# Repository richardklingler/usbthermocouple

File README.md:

# 2-channel USB thermocouple sensor

### Introduction

This is my first ever published project on Github, so most probably not error free (o;

It is a small 60mm x 80mm USB device which reads out temperatures from two K-type thermocouple sensors via MAX31855 converters.
As the main controller a STM32F070CBT6 was chosen due to the simplicity in setting up the STM32CubeIDE and configure it for USB CDC mode.

[**STM32CubeIDE**](https://www.st.com/en/development-tools/stm32cubeide.html)

For schematic and PCB design the great KiCAD software was used:

[**KiCAD**](https://www.kicad.org/)

### Repository layout

| Folder | Content |
|---|---|
| `kicad/usb_thermo_logger` | Schematic, PCB layout, 3D preview, datasheets |
| `openscad` | Front and back panels for the enclosure (`.scad` and `.stl`) |
| `stm32/USB_Thermologger_2` | Firmware, STM32CubeIDE project |
| `python` | PyQt5 logger application for the **previous** firmware (see below) |

### How it works

The device is powered from the USB port and registers as a USB CDC serial interface, so no driver is needed:

| OS | Device |
|---|---|
| Linux | `/dev/ttyACM0` |
| macOS | `/dev/cu.usbmodem…` |
| Windows | `COMx` |

The baud rate setting doesn't matter.

| USB descriptor | Value |
|---|---|
| Vendor ID / Product ID | `0x1209` / `0x5304` ([pid.codes](https://pid.codes/1209/5304/)) |
| Manufacturer | Klingler Engineering |
| Product | USB Thermocouple Logger |
| Serial number | Unique per device, derived from the STM32 chip ID |

The device doesn't send anything on its own. The host software asks for a measurement whenever it wants one, and adds its own timestamps.
This keeps the firmware simple: no clock to set, no drift, and the polling interval is completely up to the host.

The MAX31855 converts about 10 times per second, so polling faster than every 100 ms just returns the same value again.

### USB commands

| Command | Reply | Function |
|---|---|---|
| `?` | `24.50,23.75` | Read all channels |
| `*IDN?` | `Klingler Engineering,TC2,208438763130,1.0.0` | Identify the device |
| `C?` | `2` | Number of channels |
| `X1704` | none | Enter the DFU bootloader (see [Firmware update](#firmware-update)) |

Every reply is one line terminated by CR LF (`\r\n`).

Commands don't need a line ending, but **each command has to arrive in one piece**. The firmware looks at every USB packet on its own, so send the whole command with a single write.
A terminal program like `screen` sends every keystroke separately, which only works for the single-character `?`.

Send one command and wait for its reply before sending the next one.

### Identification

`*IDN?` follows the usual convention of measurement instruments and returns four comma-separated fields:

| Field | Example | Meaning |
|---|---|---|
| 1 | `Klingler Engineering` | Manufacturer |
| 2 | `TC2` | Model |
| 3 | `208438763130` | Serial number, identical to the USB serial number |
| 4 | `1.0.0` | Firmware version |

`C?` returns the number of thermocouple channels. Host software should use it instead of assuming a fixed number, so it also works with devices that have more channels.

### Reply format

After a `?`, the device replies with one line containing one value per channel, separated by commas. On the 2-channel device:

| Reply | Meaning |
|---|---|
| `24.50,23.75` | Both channels have a thermocouple |
| `24.50,-` | Only channel 1 has a valid reading |
| `-,23.75` | Only channel 2 has a valid reading |
| `-,-` | No valid reading on either channel |

Values are in degrees Celsius with a resolution of 0.25 °C. Negative temperatures are reported as negative values, e.g. `-12.25`.
The MAX31855 reports -270 °C to +1800 °C; the usable range of a K-type thermocouple itself is roughly -200 °C to +1350 °C.

### Errors

A `-` is sent for a channel when the MAX31855 reports a fault:

- thermocouple not connected (open circuit)
- thermocouple shorted to GND
- thermocouple shorted to VCC

### Quick test

With `screen` on Linux or macOS, type `?` and the reply appears (exit with Ctrl-A, then K):

```
screen /dev/ttyACM0 115200
```

For the other commands, use Python and [pyserial](https://pypi.org/project/pyserial/), which sends each command in one write:

```python
import serial

with serial.Serial('/dev/ttyACM0', timeout=1) as port:   # macOS: /dev/cu.usbmodem..., Windows: COM3
    for command in (b'*IDN?', b'C?', b'?'):
        port.write(command)
        print(command.decode(), '->', port.readline().decode().strip())
```

A simple logger that polls once per second and adds host timestamps:

```python
import serial, time
from datetime import datetime

with serial.Serial('/dev/ttyACM0', timeout=1) as port:
    while True:
        port.reset_input_buffer()
        port.write(b'?')
        reply = port.readline().decode(errors='replace').strip()
        print(f"{datetime.now().isoformat(timespec='milliseconds')},{reply}")
        time.sleep(1)
```

### Building the firmware

1. In STM32CubeIDE, use *File → Import → Existing Projects into Workspace* and select `stm32/USB_Thermologger_2`.
2. Build the *Release* configuration.
3. To get a `.bin` file for DFU flashing, enable *Project → Properties → C/C++ Build → Settings → MCU Post build outputs → Convert to binary file*.

### Firmware update

The device can be put into the STM32 DFU bootloader by sending a command, so no BOOT0 jumper or programmer is needed:

```
printf 'X1704' > /dev/ttyACM0
```

The device then re-enumerates as *STM32 BOOTLOADER* (`0483:df11`). Flash the new firmware with [dfu-util](https://dfu-util.sourceforge.net/), which is also available via Homebrew on macOS:

```
dfu-util -a 0 -s 0x08000000:leave -D stm32/USB_Thermologger_2/Release/USB_Thermologger_2.bin
```

Alternatively the firmware can be flashed directly from STM32CubeIDE with an ST-LINK via SWD.

### Changes

**September 2026**

- Project updated for current STM32CubeIDE versions and toolchains.
- The device no longer sends measurements continuously. It only replies to `?`.
- Removed the RTC time (`T`), date (`D`) and interval (`I`) commands, and the planned offset command (`O`). Timestamps, interval and calibration offsets are now the job of the host software.
- New commands `*IDN?` (identification) and `C?` (channel count).
- The device now uses its own USB ID `1209:5304` and reports as *USB Thermocouple Logger* by *Klingler Engineering*, instead of ST's generic `0483:5740`.
- Sensor faults are detected via the MAX31855 fault bit.
- Fixed negative temperatures, which were previously reported as values above 2000 °C.
- Reply lines now end with `\r\n` instead of `\n\r`.

The PyQt5 application in `python/` was written for the previous firmware (continuous output, RTC commands) and doesn't work with the current firmware.

### License

Firmware and software: GPL-3.0, see [LICENSE](LICENSE).
Hardware: CERN Open Hardware Licence v1.2, see [OSH_License.txt](OSH_License.txt).

### Donations

All my projects (currently not much but growing ;o) are self financed. If you like you can make a donation to my Paypal.me link:

paypal.me/renderingfun
[**Paypal Me Link**](https://paypal.me/renderingfun)

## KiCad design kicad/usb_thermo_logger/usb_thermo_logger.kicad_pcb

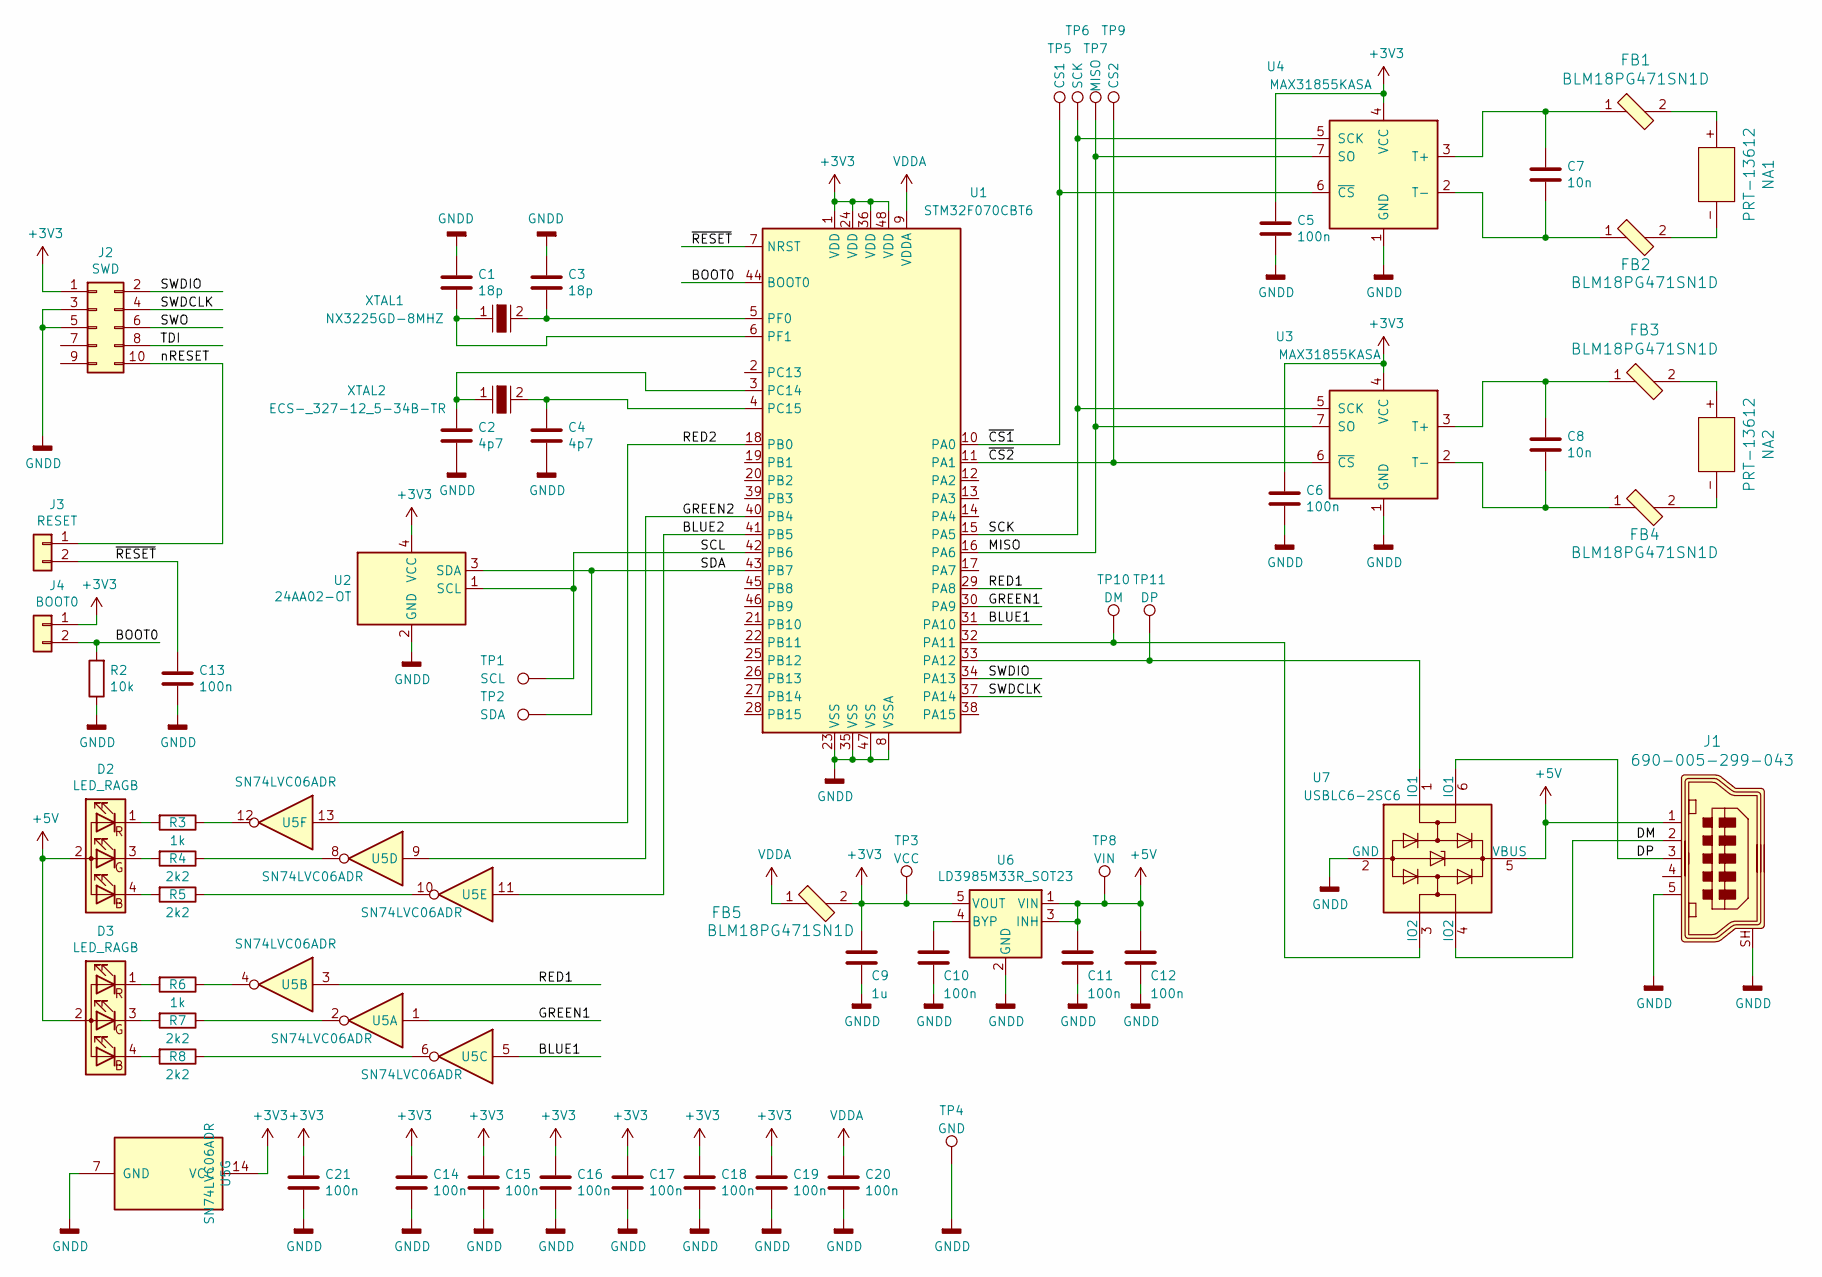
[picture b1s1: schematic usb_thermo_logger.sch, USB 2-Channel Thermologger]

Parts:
C1, C3: 18p; C_0603_1608Metric
C2, C4: 4p7; C_0603_1608Metric
C5, C6, C10, C11, C12, C13, C14, C15, C16, C17, C18, C19, C20, C21: 100n; C_0603_1608Metric
C7, C8: 10n; C_0603_1608Metric
C9: 1u; C_0603_1608Metric
D2, D3: LED_RAGB; LED_Avago_PLCC4_3.2x2.8mm_CW
FB1, FB2, FB3, FB4, FB5: BLM18PG471SN1D; 0603; MPN BLM18PG471SN1D; Digi-Key_PN 490-5223-1-ND
J1: 690-005-299-043; USB_Mini_B_Female_690-005-299-043; MPN 690-005-299-043; Digi-Key_PN 151-1206-1-ND
J2: SWD; PinHeader_2x05_P1.27mm_Vertical_SMD
J3: RESET; PinHeader_1x02_P2.54mm_Vertical
J4: BOOT0; PinHeader_1x02_P2.54mm_Vertical
NA1, NA2: PRT-13612; Thermocouple_Connector_PCC-SMP-K; MPN PRT-13612; Digi-Key_PN 1568-1306-ND
R2: 10k; R_0603_1608Metric
R3, R6: 1k; R_0603_1608Metric
R4, R5, R7, R8: 2k2; R_0603_1608Metric
TP1: SCL; TestPoint_Pad_1.0x1.0mm
TP2: SDA; TestPoint_Pad_1.0x1.0mm
TP3: VCC; TestPoint_Pad_1.0x1.0mm
TP4: GND; TestPoint_Pad_1.0x1.0mm
TP5: CS1; TestPoint_Pad_1.0x1.0mm
TP6: SCK; TestPoint_Pad_1.0x1.0mm
TP7: MISO; TestPoint_Pad_1.0x1.0mm
TP8: VIN; TestPoint_Pad_1.0x1.0mm
TP9: CS2; TestPoint_Pad_1.0x1.0mm
TP10: DM; TestPoint_Pad_1.0x1.0mm
TP11: DP; TestPoint_Pad_1.0x1.0mm
U1: STM32F070CBT6; LQFP-48_7x7mm_P0.5mm
U2: 24AA02-OT; SOT-23-5
U3, U4: MAX31855KASA; SOIC-8_3.9x4.9mm_P1.27mm
U5: SN74LVC06ADR; SOIC-14_3.9x8.7mm_P1.27mm; Digikey 296-14905-1-ND
U6: LD3985M33R_SOT23; SOT-23-5
U7: USBLC6-2SC6; SOT-23-6
XTAL1: NX3225GD-8MHZ; SMD-2_3.2x2.5mm; MPN NX3225GD-8MHZ-STD-CRA-3; Digi-Key_PN 644-1178-1-ND
XTAL2: ECS-_327-12_5-34B-TR; SMD-2_3.2x1.5mm; MPN ECS-.327-12.5-34B-TR; Digi-Key_PN XC1617CT-ND

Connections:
+3V3: C5.1, C6.1, C9.1, C14.1, C15.1, C16.1, C17.1, C18.1, C19.1, C21.1, FB5.2, J2.1, J4.1, TP3.1, U1.1 (VDD), U1.24 (VDD), U1.36 (VDD), U1.48 (VDD), U2.4 (VCC), U3.4 (VCC), U4.4 (VCC), U5.14 (VCC), U6.5 (VOUT)
+5V: C11.1, C12.1, D2.2 (A), D3.2 (A), J1.1, TP8.1, U6.1 (VIN), U6.3 (INH), U7.5 (VBUS)
/BLUE1: U1.31 (PA10), U5.5
/BLUE2: U1.41 (PB5), U5.11
/BOOT0: J4.2, R2.2, U1.44 (BOOT0)
/DM: J1.2, U7.4 (IO2)
/DP: J1.3, U7.6 (IO1)
/GREEN1: U1.30 (PA9), U5.1
/GREEN2: U1.40 (PB4), U5.9
/MISO: TP7.1, U1.16 (PA6), U3.7 (SO), U4.7 (SO)
/RED1: U1.29 (PA8), U5.3
/RED2: U1.18 (PB0), U5.13
/SCK: TP6.1, U1.15 (PA5), U3.5 (SCK), U4.5 (SCK)
/SCL: TP1.1, U1.42 (PB6), U2.1 (SCL)
/SDA: TP2.1, U1.43 (PB7), U2.3 (SDA)
/SWDCLK: J2.4, U1.37 (PA14)
/SWDIO: J2.2, U1.34 (PA13)
/SWO: J2.6
/TDI: J2.8
/nRESET: J2.10, J3.1
/~CS1: TP5.1, U1.10 (PA0), U4.6 (~CS~)
/~CS2: TP9.1, U1.11 (PA1), U3.6 (~CS~)
/~RESET: C13.1, J3.2, U1.7 (NRST)
GNDD: C1.1, C2.2, C3.1, C4.2, C5.2, C6.2, C9.2, C10.2, C11.2, C12.2, C13.2, C14.2, C15.2, C16.2, C17.2, C18.2, C19.2, C20.2, C21.2, J1.5, J1.SH, J2.3, J2.5, R2.1, TP4.1, U1.8 (VSSA), U1.23 (VSS), U1.35 (VSS), U1.47 (VSS), U2.2 (GND), U3.1 (GND), U4.1 (GND), U5.7 (GND), U6.2 (GND), U7.2 (GND)
unnamed: C1.2, U1.6 (PF1), XTAL1.1
unnamed: C2.1, U1.3 (PC14), XTAL2.1
unnamed: C3.2, U1.5 (PF0), XTAL1.2
unnamed: C4.1, U1.4 (PC15), XTAL2.2
unnamed: C7.1, FB1.1, U4.3 (T+)
unnamed: C7.2, FB2.1, U4.2 (T-)
unnamed: C8.1, FB3.1, U3.3 (T+)
unnamed: C8.2, FB4.1, U3.2 (T-)
unnamed: C10.1, U6.4 (BYP)
unnamed: D2.1 (RK), R3.2
unnamed: D2.3 (GK), R4.2
unnamed: D2.4 (BK), R5.2
unnamed: D3.1 (RK), R6.2
unnamed: D3.3 (GK), R7.2
unnamed: D3.4 (BK), R8.2
unnamed: FB1.2, NA1.+
unnamed: FB2.2, NA1.-
unnamed: FB3.2, NA2.+
unnamed: FB4.2, NA2.-
unnamed: R3.1, U5.12
unnamed: R4.1, U5.8
unnamed: R5.1, U5.10
unnamed: R6.1, U5.4
unnamed: R7.1, U5.2
unnamed: R8.1, U5.6
unnamed: TP10.1, U1.32 (PA11), U7.3 (IO2)
unnamed: TP11.1, U1.33 (PA12), U7.1 (IO1)
VDDA: C20.1, FB5.1, U1.9 (VDDA)

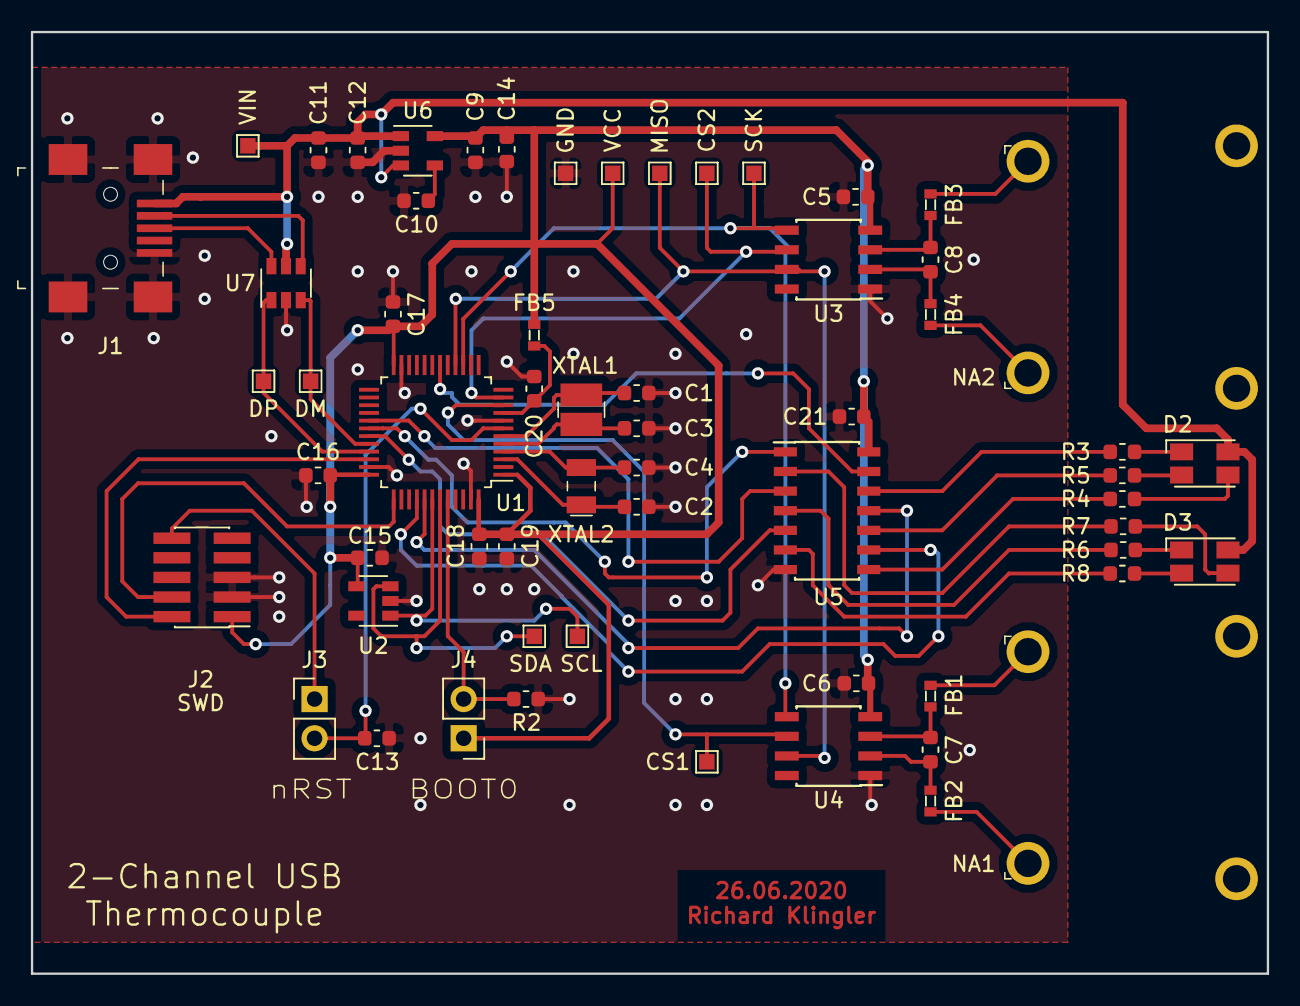
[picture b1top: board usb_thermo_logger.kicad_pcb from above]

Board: 2 copper layers, 80.0 x 61.0 mm, 61 parts (0 on the bottom side), 50 nets.

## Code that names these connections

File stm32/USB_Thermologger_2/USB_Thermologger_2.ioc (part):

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Mcu.Name=STM32F070CBTx
Mcu.Package=LQFP48
Mcu.UserName=STM32F070CBTx
PA0.GPIOParameters=GPIO_Label
PA0.GPIO_Label=MAX1
PA0.Signal=GPIO_Output
PA1.GPIOParameters=GPIO_Label
PA1.GPIO_Label=MAX2
PA1.Signal=GPIO_Output
PA11.Mode=Device
PA11.Signal=USB_DM
PA12.Mode=Device
PA12.Signal=USB_DP
PA13.Mode=Serial_Wire
PA13.Signal=SYS_SWDIO
PA14.Mode=Serial_Wire
PA14.Signal=SYS_SWCLK
PA5.Mode=RX_Only_Simplex_Unidirect_Master
PA5.Signal=SPI1_SCK
PA6.Mode=RX_Only_Simplex_Unidirect_Master
PA6.Signal=SPI1_MISO
PB6.GPIOParameters=GPIO_Pu
PB6.GPIO_Pu=GPIO_PULLUP
PB6.Mode=I2C
PB6.Signal=I2C1_SCL
PB7.GPIOParameters=GPIO_Pu
PB7.GPIO_Pu=GPIO_PULLUP
PB7.Mode=I2C
PB7.Signal=I2C1_SDA
PC14-OSC32_IN.Mode=LSE-External-Oscillator
PC14-OSC32_IN.Signal=RCC_OSC32_IN
PC15-OSC32_OUT.Mode=LSE-External-Oscillator
PC15-OSC32_OUT.Signal=RCC_OSC32_OUT
PF0-OSC_IN.Mode=HSE-External-Oscillator
PF0-OSC_IN.Signal=RCC_OSC_IN
PF1-OSC_OUT.Mode=HSE-External-Oscillator
PF1-OSC_OUT.Signal=RCC_OSC_OUT
RCC.SYSCLKFreq_VALUE=48000000
RCC.SYSCLKSource=RCC_SYSCLKSOURCE_PLLCLK
board=custom

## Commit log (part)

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2020-06-12 Added KiCAD design
2020-06-12 Added STM32CubeIDE project
2020-06-12 Added OSH license
2020-06-13 Added DFU flashing description
2020-06-14 LED display changes, added OpenSCAD
2020-06-29 Layout changes
2020-06-29 3D preview update
2020-06-29 Changed description
2020-07-18 Added back panel openscad design
2020-08-28 Added PyQt5 sample application for logging data
2020-08-28 README.md update
